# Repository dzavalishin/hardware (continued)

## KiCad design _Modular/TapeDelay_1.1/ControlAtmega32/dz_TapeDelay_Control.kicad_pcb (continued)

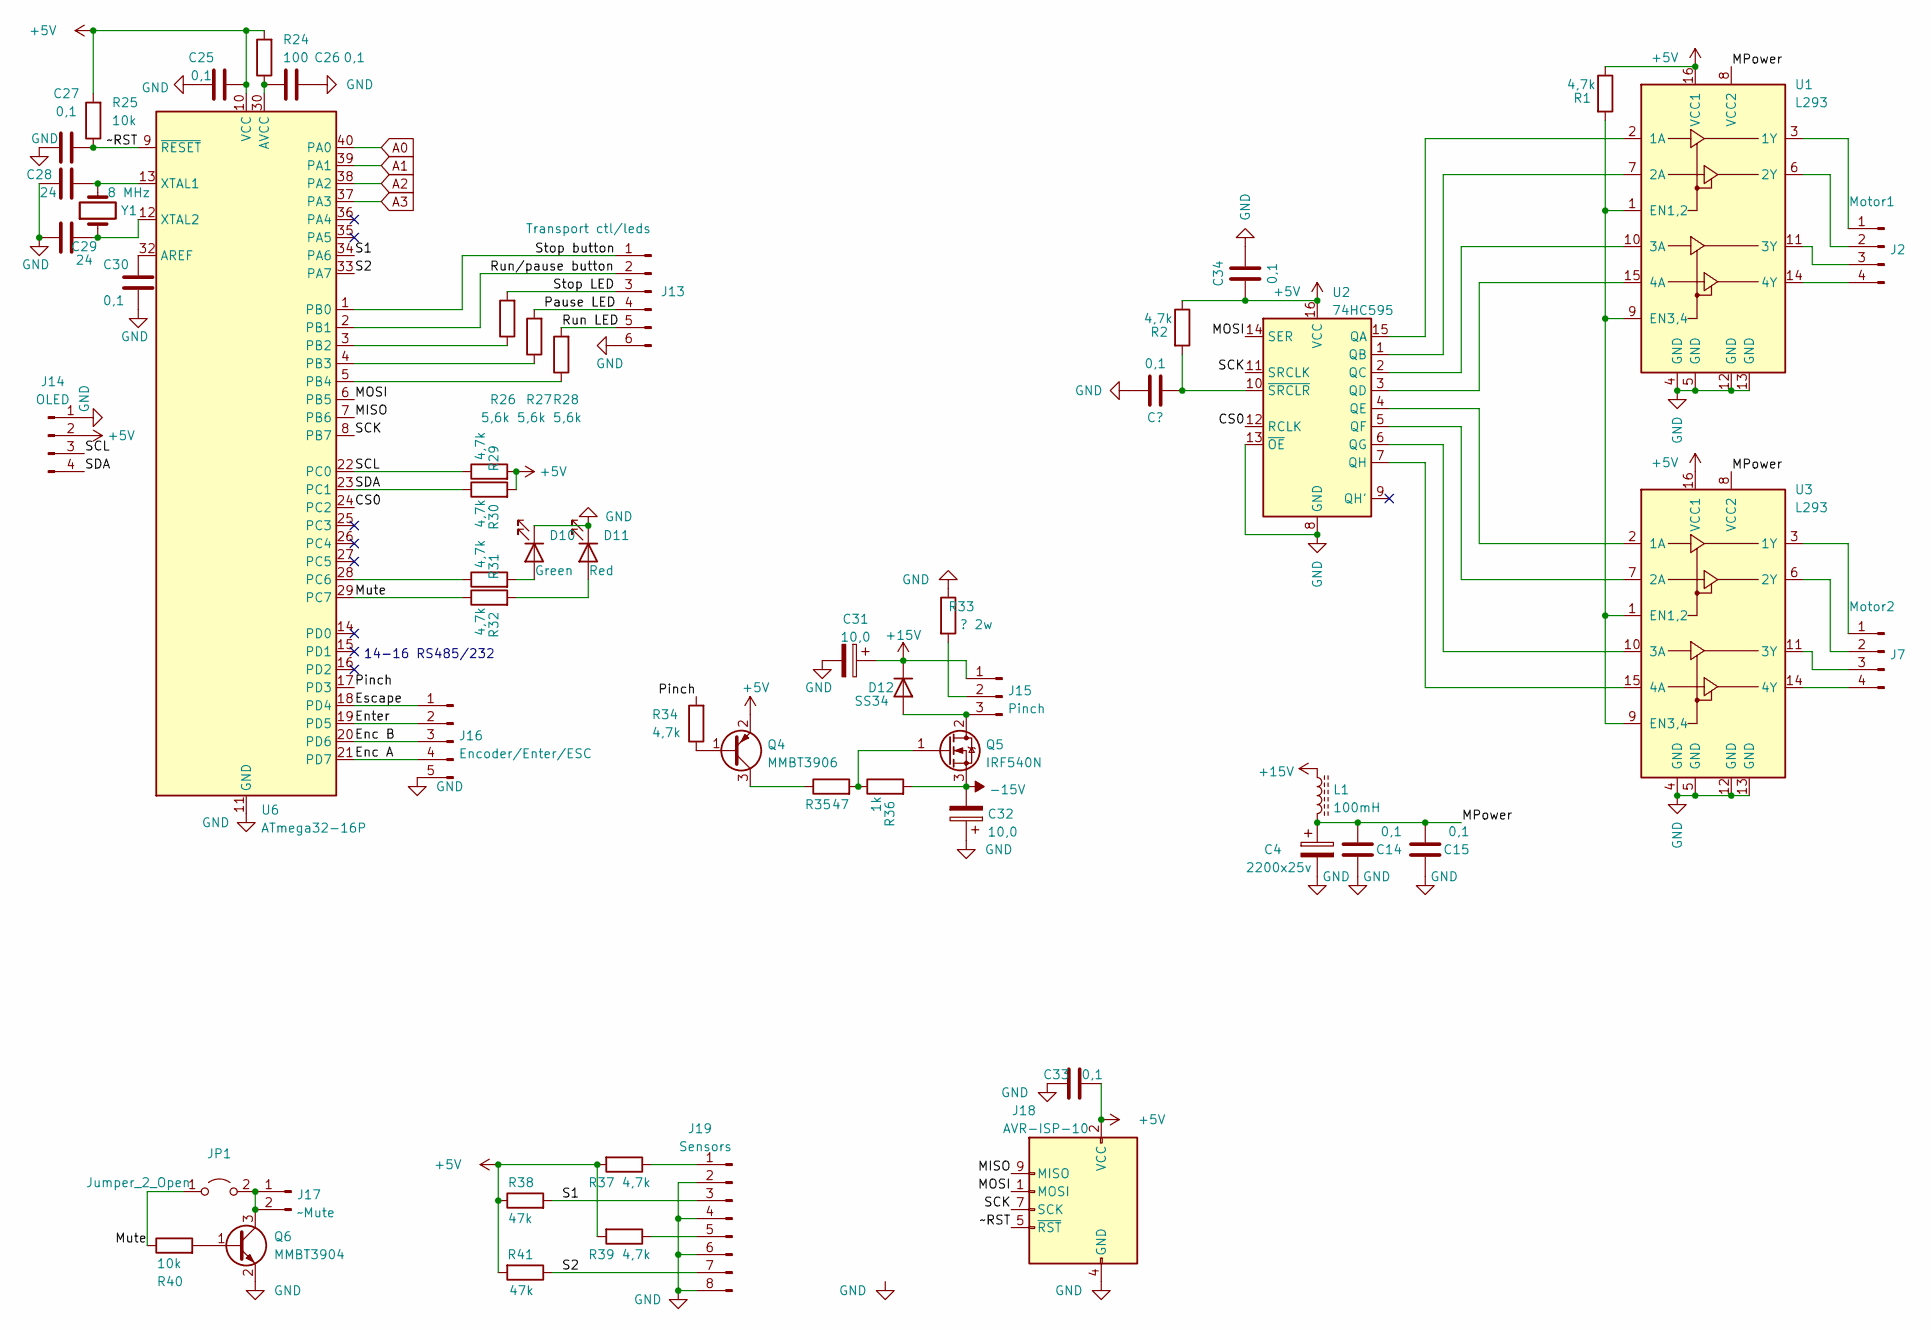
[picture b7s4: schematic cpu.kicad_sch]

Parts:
C4: 2200x25v; CP_Radial_D13.0mm_P5.00mm
C14, C15, C25, C26, C27, C30, C33, C34: 0,1; C_1206_3216Metric_Pad1.33x1.80mm_HandSolder
C28, C29: 24; C_Disc_D5.0mm_W2.5mm_P2.50mm
C31, C32: 10,0; CP_Radial_D6.3mm_P2.50mm
D10: Green; LED_1206_3216Metric_Pad1.42x1.75mm_HandSolder
D11: Red; LED_1206_3216Metric_Pad1.42x1.75mm_HandSolder
D12: SS34; D_SMA-SMB_Universal_Handsoldering
J2: Motor1; PinHeader_1x04_P2.54mm_Vertical
J7: Motor2; PinHeader_1x04_P2.54mm_Vertical
J13: Transport ctl/leds; PinHeader_1x06_P2.54mm_Vertical
J14: OLED; PinHeader_1x04_P2.54mm_Vertical
J15: Pinch; PinHeader_1x03_P2.54mm_Vertical
J16: Encoder/Enter/ESC; PinHeader_1x05_P2.54mm_Vertical
J17: ~Mute; PinHeader_1x02_P2.54mm_Vertical
J18: AVR-ISP-10; PinHeader_2x05_P2.54mm_Vertical
J19: Sensors; PinHeader_1x08_P2.54mm_Vertical
JP1: Jumper_2_Open; PinHeader_1x02_P2.54mm_Vertical
L1: 100mH; L_Toroid_Vertical_L10.0mm_W5.0mm_P5.08mm
Q4: MMBT3906; SOT-23
Q5: IRF540N; TO-220-3_Vertical
Q6: MMBT3904; SOT-23
R1, R2, R29, R30, R31, R32, R34, R37, R39: 4,7k; R_1206_3216Metric_Pad1.30x1.75mm_HandSolder
R24: 100; R_1206_3216Metric_Pad1.30x1.75mm_HandSolder
R25, R40: 10k; R_1206_3216Metric_Pad1.30x1.75mm_HandSolder
R26, R27, R28: 5,6k; R_1206_3216Metric_Pad1.30x1.75mm_HandSolder
R33: ? 2w; R_Axial_DIN0309_L9.0mm_D3.2mm_P2.54mm_Vertical
R35: 47; R_1206_3216Metric_Pad1.30x1.75mm_HandSolder
R36: 1k; R_1206_3216Metric_Pad1.30x1.75mm_HandSolder
R38, R41: 47k; R_1206_3216Metric_Pad1.30x1.75mm_HandSolder
U1, U3: L293; DIP-16_W7.62mm_Socket_LongPads
U2: 74HC595; DIP-16_W7.62mm_Socket_LongPads
U6: ATmega32-16P; DIP-40_W15.24mm_Socket_LongPads
Y1: 8 MHz; Crystal_HC49-U_Vertical

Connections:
+5V: C25.2, C33.2, C34.1, J14.2, J18.2 (VCC), Q4.2 (E), R1.1, R2.1, R24.2, R25.2, R29.2, R30.2, R37.2, R38.1, R39.2, R41.2, U1.16 (VCC1), U2.16 (VCC), U3.16 (VCC1), U6.10 (VCC); also elsewhere on the board
+15V: C31.1, D12.1 (K), J15.1, L1.1; also elsewhere on the board
-15V: C32.2, Q5.3 (S), R36.2; also elsewhere on the board
/CPU/CS0: U2.12 (RCLK), U6.24 (PC2)
/CPU/Enc A: J16.4, U6.21 (PD7)
/CPU/Enc B: J16.3, U6.20 (PD6)
/CPU/Enter: J16.2, U6.19 (PD5)
/CPU/Escape: J16.1, U6.18 (PD4)
/CPU/MISO: J18.9 (MISO), U6.7 (PB6)
/CPU/MOSI: J18.1 (MOSI), U2.14 (SER), U6.6 (PB5)
/CPU/MPower: C4.1, C14.2, C15.2, L1.2, U1.8 (VCC2), U3.8 (VCC2)
/CPU/Mute: JP1.1 (A), R32.1, R40.1, U6.29 (PC7)
/CPU/Pause LED: J13.4, R27.2
/CPU/Pinch: R34.2, U6.17 (PD3)
/CPU/Run LED: J13.5, R28.2
/CPU/Run/pause button: J13.2, U6.2 (PB1)
/CPU/S1: J19.3, R38.2, U6.34 (PA6)
/CPU/S2: J19.7, R41.1, U6.33 (PA7)
/CPU/SCK: J18.7 (SCK), U2.11 (SRCLK), U6.8 (PB7)
/CPU/SCL: J14.3, R29.1, U6.22 (PC0)
/CPU/SDA: J14.4, R30.1, U6.23 (PC1)
/CPU/Stop LED: J13.3, R26.2
/CPU/Stop button: J13.1, U6.1 (PB0)
/CPU/~RST: C27.2, J18.5 (~RST), R25.1, U6.9 (~RESET)
A0: U6.40 (PA0); also elsewhere on the board
A1: U6.39 (PA1); also elsewhere on the board
A2: U6.38 (PA2); also elsewhere on the board
A3: U6.37 (PA3); also elsewhere on the board
GND: C4.2, C14.1, C15.1, C25.1, C26.2, C27.1, C28.2, C29.2, C30.2, C31.2, C32.1, C33.1, C34.2, D10.1 (K), D11.1 (K), J13.6, J14.1, J16.5, J18.4 (GND), J18.6 (GND), J18.8 (GND), J18.10 (GND), J19.2, J19.4, J19.6, J19.8, Q6.2 (E), R33.1, U1.4 (GND), U1.5 (GND), U1.12 (GND), U1.13 (GND), U2.8 (GND), U2.13 (~OE), U3.4 (GND), U3.5 (GND), U3.12 (GND), U3.13 (GND), U6.11 (GND), U6.31 (GND); also elsewhere on the board
unnamed: C26.1, R24.1, U6.30 (AVCC)
unnamed: C28.1, U6.13 (XTAL1), Y1.2
unnamed: C29.1, U6.12 (XTAL2), Y1.1
unnamed: C30.1, U6.32 (AREF)
unnamed: D10.2 (A), R31.2
unnamed: D11.2 (A), R32.2
unnamed: D12.2 (A), J15.3, Q5.2 (D)
unnamed: J2.1, U1.3 (1Y)
unnamed: J2.2, U1.6 (2Y)
unnamed: J2.3, U1.11 (3Y)
unnamed: J2.4, U1.14 (4Y)
unnamed: J7.1, U3.3 (1Y)
unnamed: J7.2, U3.6 (2Y)
unnamed: J7.3, U3.11 (3Y)
unnamed: J7.4, U3.14 (4Y)
unnamed: J15.2, R33.2
unnamed: J17.1, J17.2, JP1.2 (B), Q6.3 (C)
unnamed: J19.1, R37.1
unnamed: J19.5, R39.1
unnamed: Q4.1 (B), R34.1
unnamed: Q4.3 (C), R35.1
unnamed: Q5.1 (G), R35.2, R36.1
unnamed: Q6.1 (B), R40.2
unnamed: R1.2, U1.1 (EN1,2), U1.9 (EN3,4), U3.1 (EN1,2), U3.9 (EN3,4)
unnamed: R2.2, U2.10 (~SRCLR)
unnamed: R26.1, U6.3 (PB2)
unnamed: R27.1, U6.4 (PB3)
unnamed: R28.1, U6.5 (PB4)
unnamed: R31.1, U6.28 (PC6)
unnamed: U1.2 (1A), U2.15 (QA)
unnamed: U1.7 (2A), U2.1 (QB)
unnamed: U1.10 (3A), U2.2 (QC)
unnamed: U1.15 (4A), U2.3 (QD)
unnamed: U2.4 (QE), U3.2 (1A)
unnamed: U2.5 (QF), U3.7 (2A)
unnamed: U2.6 (QG), U3.10 (3A)
unnamed: U2.7 (QH), U3.15 (4A)

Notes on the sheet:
14-16 RS485/232

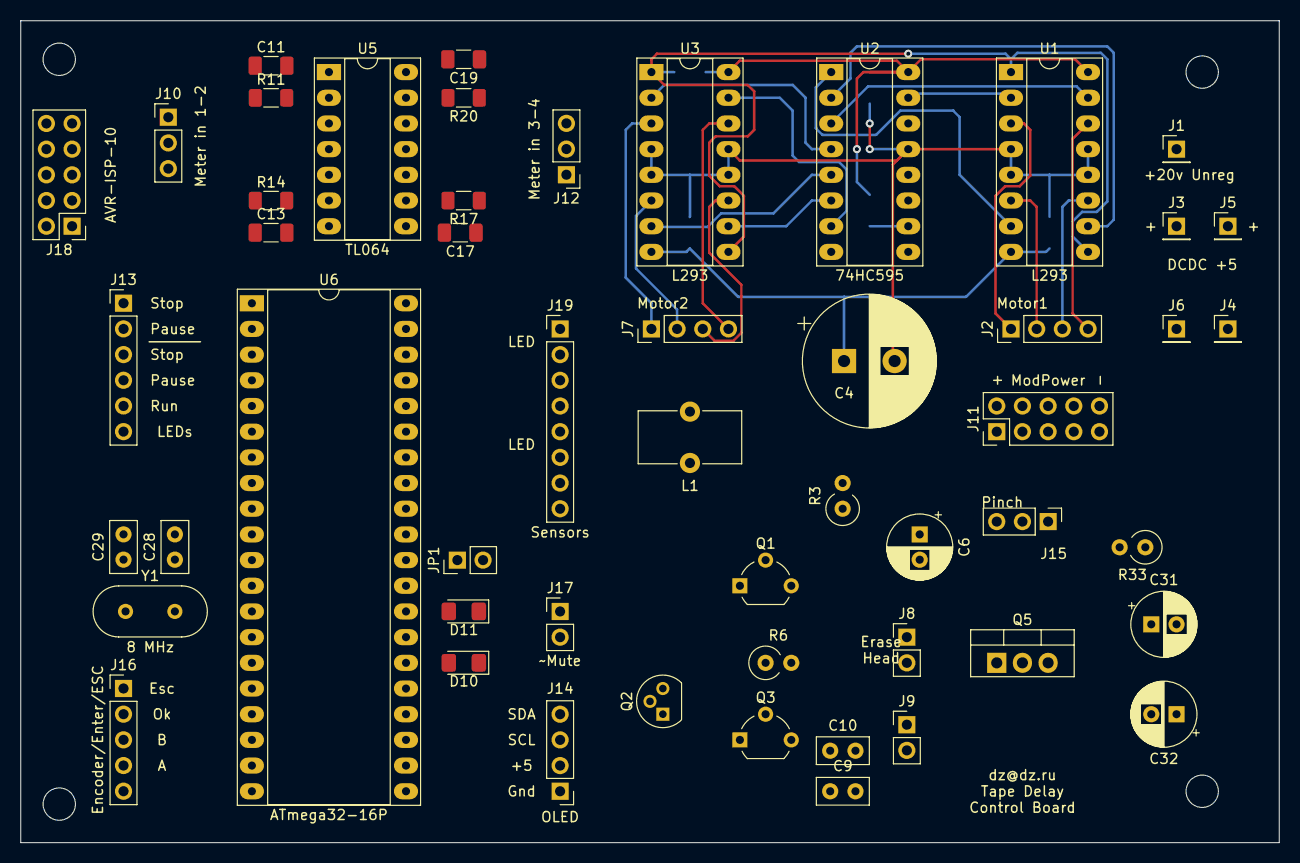
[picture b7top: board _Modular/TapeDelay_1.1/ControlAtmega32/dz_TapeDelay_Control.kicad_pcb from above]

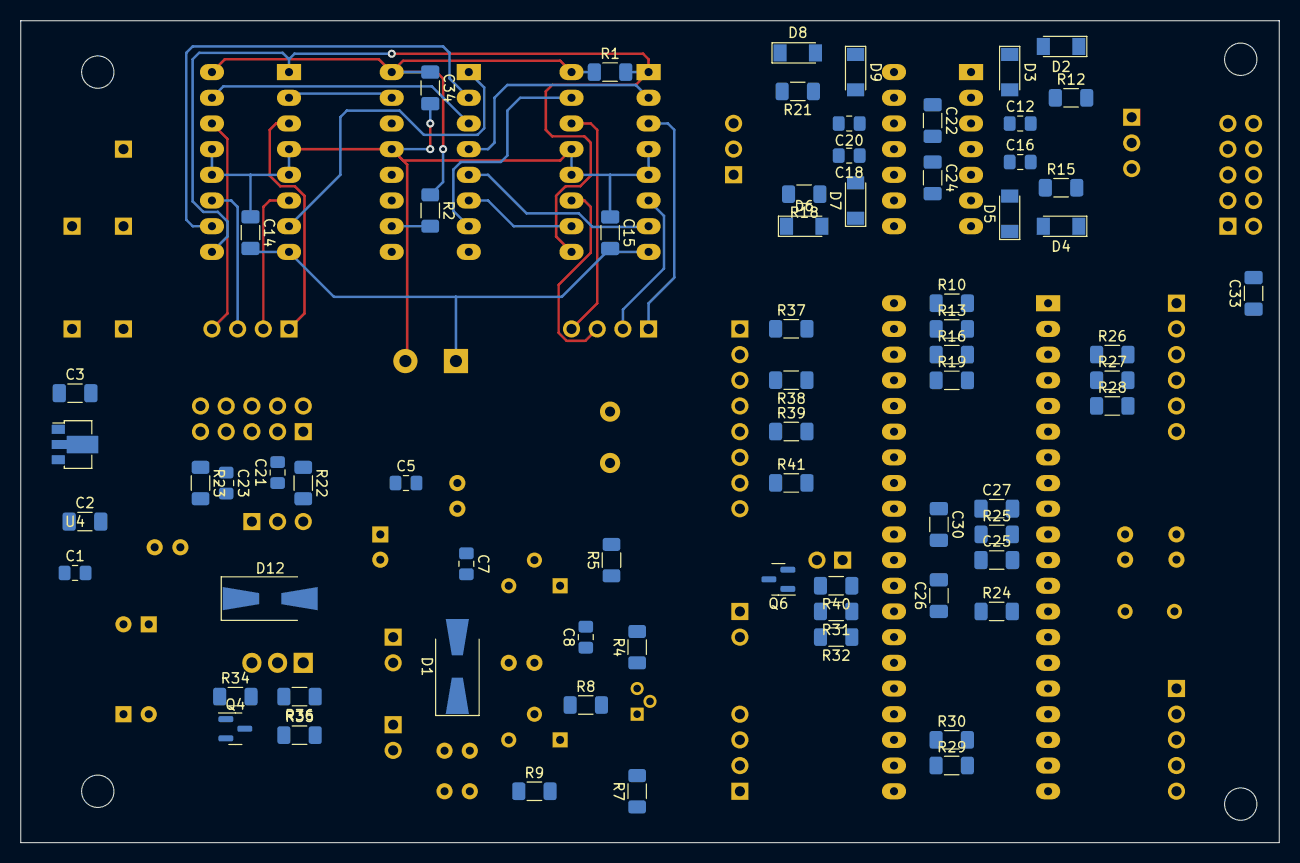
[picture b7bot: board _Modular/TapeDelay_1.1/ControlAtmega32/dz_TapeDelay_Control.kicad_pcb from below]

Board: 2 copper layers, 124.5 x 81.3 mm, 125 parts (69 on the bottom side), 97 nets.
